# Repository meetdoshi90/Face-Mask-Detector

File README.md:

<h1 align="center">:dna: Face Mask Detection using R-Pi :dna:</h1>
<h3 align="center">A Low Cost Portable Raspberry-Pi Face Mask Detector with live feed</h3>

## WebPage and Hardware

### Live feed Webpage

### Project Flowchart

### Neural Network Architecture

<!-- GETTING STARTED -->
## Getting Started

**Hardware and basic setup guide.**

### Hardware Setup
  **List of Components**

### Prerequisites

This is an example of how to list things you need to use the software and how to install them.
* Raspberry Pi OS
  ```sh
  > https://www.raspberrypi.org/software/operating-systems/
  ```
* Ethcer
  ```sh
  > https://www.balena.io/etcher/
  ```
* Tensorflow Lite
  ```sh
  > pip3 install https://dl.google.com/coral/python/tflite_runtime-2.1.0.post1-cp37-cp37m-linux_armv7l.whl
  ```
* OpenCV Dependencies
  ```sh
  > sudo apt-get update && sudo apt-get upgrade
  > sudo apt-get install build-essential cmake unzip pkg-config
  > sudo apt-get install libjpeg-dev libpng-dev libtiff-dev
  > sudo apt-get install libavcodec-dev libavformat-dev libswscale-dev libv4l-dev
  > sudo apt-get install libxvidcore-dev libx264-dev
  > sudo apt-get install libgtk-3-dev
  > sudo apt-get install libcanberra-gtk*
  > sudo apt-get install libatlas-base-dev gfortran
  > sudo apt-get install python3-dev
  ```
* OpenCV 4
  ```sh
  > cd ~
  > wget -O opencv.zip https://github.com/opencv/opencv/archive/4.3.0.zip
  > wget -O opencv_contrib.zip
  > https://github.com/opencv/opencv_contrib/archive/4.3.0.zip unzip opencv.zip
  > unzip opencv_contrib.zip
  > mv opencv-4.0.0 opencv
  > mv opencv_contrib-4.0.0 opencv_contrib
  ```
* Numpy
  ```sh
  > pip3 install numpy
  ```
* CMake and compile OpenCV 4
  ```sh
  > cd ~/opencv
  > mkdir build
  > cd build
  > cmake -D CMAKE_BUILD_TYPE=RELEASE \-D CMAKE_INSTALL_PREFIX=/usr/local \
    -D OPENCV_EXTRA_MODULES_PATH=~/opencv_contrib/modules \
    -D ENABLE_NEON=ON \
    -D ENABLE_VFPV3=ON \
    -D BUILD_TESTS=OFF \
    -D OPENCV_ENABLE_NONFREE=ON \
    -D INSTALL_PYTHON_EXAMPLES=OFF \
    -D BUILD_EXAMPLES=OFF ..
  > make -j4
  > sudo make install
  > sudo ldconfig 

### Installation

1. Clone the repo
   ```sh
   > git clone git@github.com:meetdoshi90/Face-Mask-Detector.git
   ```
2. Install Requirements
   ```sh
   > cd rpi_based_mask_detector_new
   > pip3 install -r requirements.txt
   ```

## Built With

- Python
- Flask
- Tensorflow
- OpenCV
- HTML
- CSS
- JavaScript

## Live Demo

[Live Demo Link](https://www.youtube.com/watch?v=nb4apwK3eP4)

## Authors

👤 **Meet Doshi**

- GitHub: [@meetdoshi90](https://github.com/meetdoshi90)
- LinkedIn: [@meetdoshi90](https://linkedin.com/in/meetdoshi90)

👤 **Shravani Dhote**

## 🤝 Contributing

Contributions, issues, and feature requests are welcome!

Feel free to check the [issues page](../../issues/).

## Show your support

Give a ⭐️ if you like this project!

## 📝 License

This project is [MIT](./MIT.md) licensed.

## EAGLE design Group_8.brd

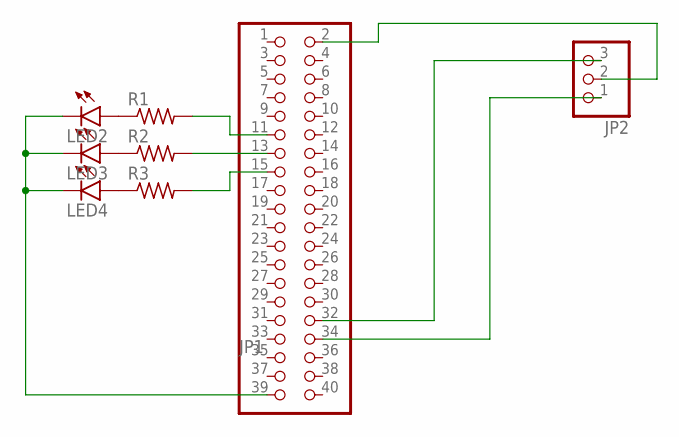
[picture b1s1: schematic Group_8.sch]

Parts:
JP1: PINHD-2X20; 2X20
JP2: PINHD-1X3; 1X03
LED2, LED3, LED4: LED5MM
R1, R2, R3: R-US_0204/7; 0204/7

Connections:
unnamed: JP1.34, JP2.1
unnamed: JP1.32, JP2.3
unnamed: LED4.A, R3.1
unnamed: LED2.A, R1.1
unnamed: LED3.A, R2.1
unnamed: JP1.11, R1.2
unnamed: JP1.13, R2.2
unnamed: JP1.15, R3.2
unnamed: JP1.2, JP2.2
unnamed: JP1.39, LED2.K (C), LED3.K (C), LED4.K (C)

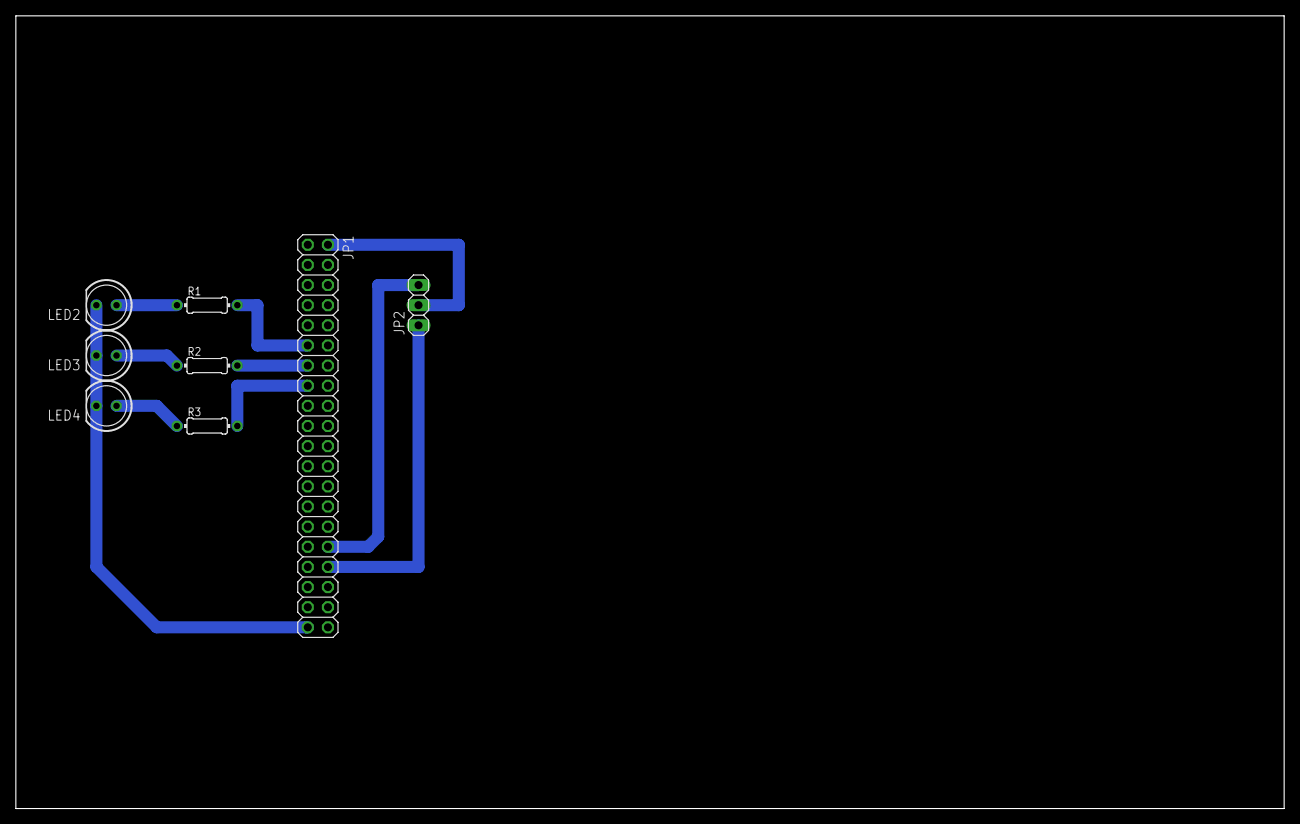
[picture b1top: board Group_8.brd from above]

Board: 2 copper layers, 160.0 x 100.0 mm, 8 parts (0 on the bottom side), 10 nets.

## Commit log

2021-04-11 PCB Files
2021-04-15 Face-Mask Module Added
2021-04-15 Flask Files
2021-04-15 All files
2021-04-22 Deleted
2021-04-23 Scaled changed to 2.5
2021-05-04 Final Commit
2021-09-12 Create LICENSE
2021-09-12 Rearranged Folders

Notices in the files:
README.md:
License: MIT
